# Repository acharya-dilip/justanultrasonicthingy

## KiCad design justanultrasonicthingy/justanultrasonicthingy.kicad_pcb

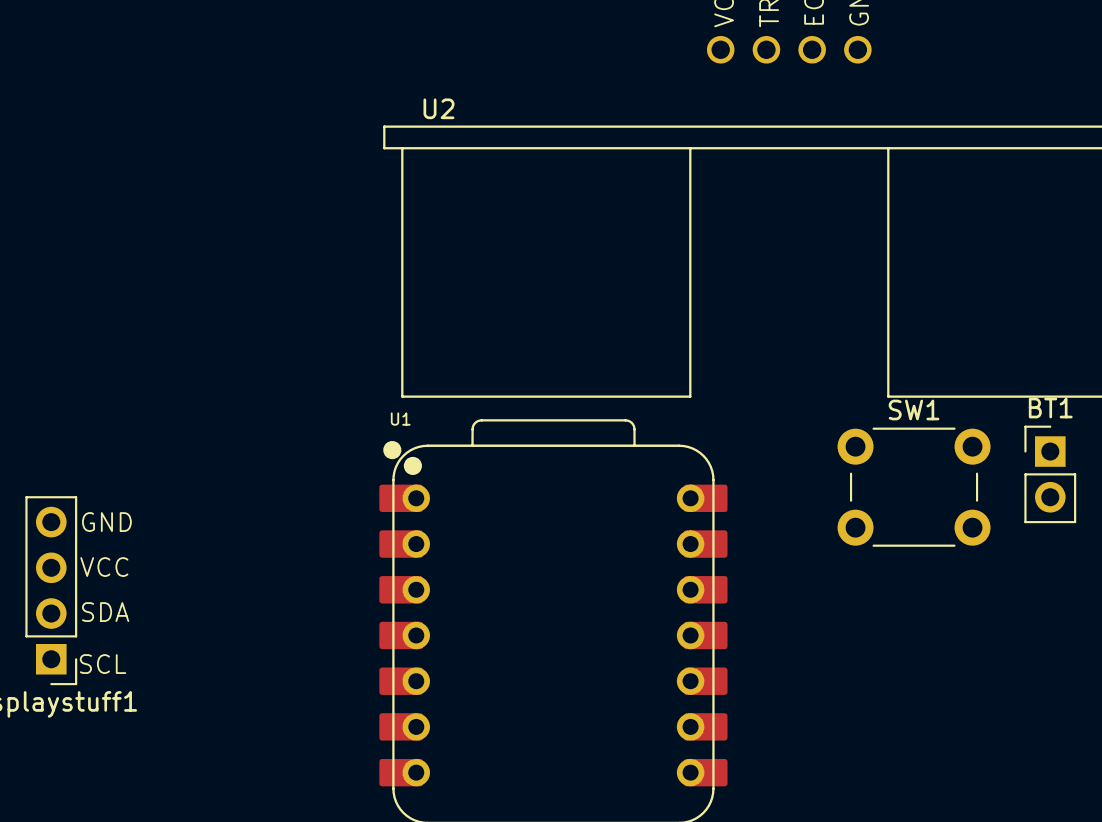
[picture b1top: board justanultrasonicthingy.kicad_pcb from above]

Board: 2 copper layers, 5 parts (0 on the bottom side), 7 nets, no tracks yet.

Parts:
BT1: Battery; PinHeader_1x02_P2.54mm_Vertical
Displaystuff1: Conn_01x04_Pin; PinHeader_1x04_P2.54mm_Vertical
SW1: SW_Push; SW_PUSH_6mm
U1: XIAO-RP2040-DIP
U2: HC-SR04; XCVR_HC-SR04

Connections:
GND: BT1.2 (-), Displaystuff1.4, U1.13 (GND), U2.4 (GND)
unnamed: BT1.1 (+), SW1.1
SCL: Displaystuff1.1, U1.6 (GPIO7/SCL)
SDA: Displaystuff1.2, U1.5 (GPIO6/SDA)
echo: U1.3 (GPIO28/ADC2/A2), U2.3 (ECHO)
powah: Displaystuff1.3, SW1.2, U1.14 (VBUS), U2.1 (VCC)
trig: U1.2 (GPIO27/ADC1/A1), U2.2 (TRIG)

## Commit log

2025-08-09 Created the Kicad files
2025-08-09 Wired the simple ultrasonic sensor to the xiao board
2025-08-09 Added 4 pin holes for the display stuff and two pin holes for the battery
2025-08-09 Added all the stuff with a few workarounds
2025-08-10 Added Resistors for the components
2025-08-10 Added a small led indicator for the pcb when it is turned on
2025-08-10 Added the laser stuff in the pcb
